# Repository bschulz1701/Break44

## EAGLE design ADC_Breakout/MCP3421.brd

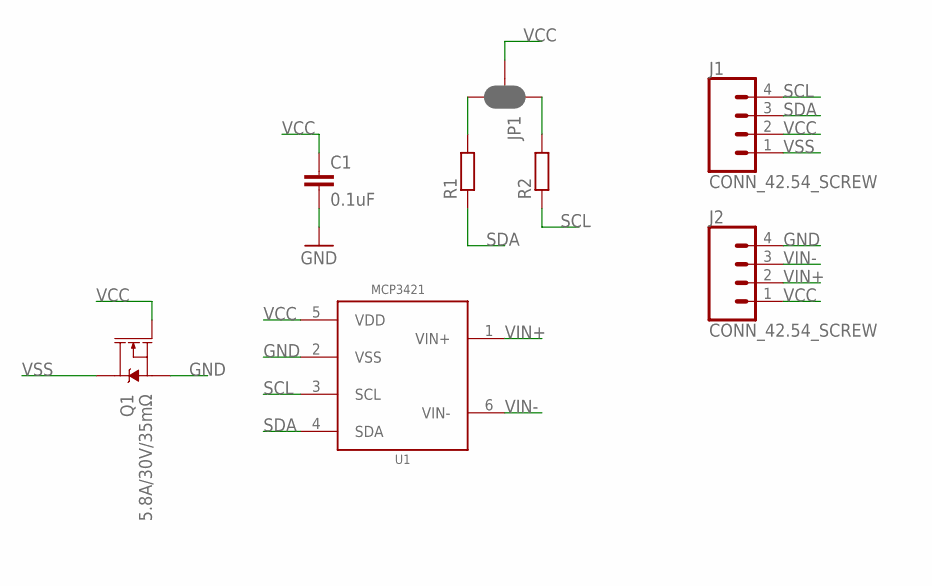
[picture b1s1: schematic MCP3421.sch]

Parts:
C1: 0.1uF; C0603
J1, J2: CONN_42.54_SCREW; 1X04_SCREW
JP1: JUMPER-SMT_3_2-NC_PASTE_SILK; SMT-JUMPER_3_2-NC_PASTE_SILK
Q1: 5.8A/30V/35mΩ; SOT23-3
R1, R2: R-EU_10KR0603; R0603
U1: MCP3421A3; SOT23-6L

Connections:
GND: C1.2, J2.4, Q1.2 (S), U1.2 (VSS)
unnamed: JP1.3, R1.2
unnamed: JP1.1, R2.2
SCL: J1.4, R2.1, U1.3 (SCL)
SDA: J1.3, R1.1, U1.4 (SDA)
VCC: C1.1, J1.2, J2.1, JP1.2, Q1.1 (G), U1.5 (VDD)
VIN+: J2.2, U1.1 (VIN+)
VIN-: J2.3, U1.6 (VIN-)
VSS: J1.1, Q1.3 (D)

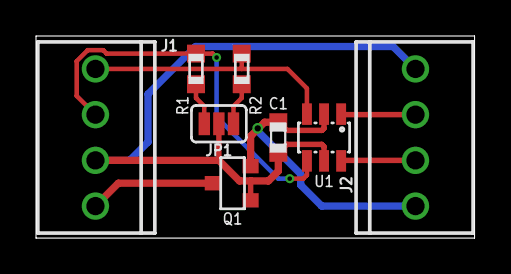
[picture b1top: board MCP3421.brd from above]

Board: 2 copper layers, 24.4 x 11.2 mm, 8 parts (0 on the bottom side), 9 nets.

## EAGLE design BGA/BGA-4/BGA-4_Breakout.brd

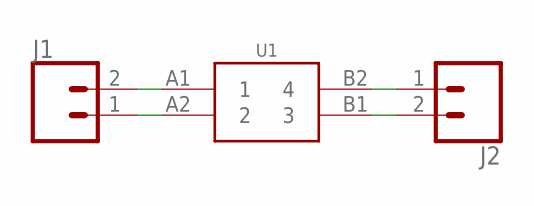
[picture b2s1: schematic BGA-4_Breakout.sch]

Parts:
J1, J2: CONN_02; 1X02
U1: GEN_4BGA; YFP0004

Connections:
unnamed: J2.1, U1.B2 (4)
unnamed: J2.2, U1.B1 (3)
unnamed: J1.1, U1.A2 (2)
unnamed: J1.2, U1.A1 (1)

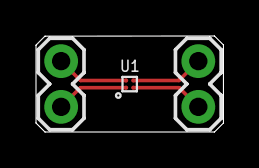
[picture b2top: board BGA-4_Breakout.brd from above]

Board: 2 copper layers, 10.4 x 5.3 mm, 3 parts (0 on the bottom side), 4 nets.

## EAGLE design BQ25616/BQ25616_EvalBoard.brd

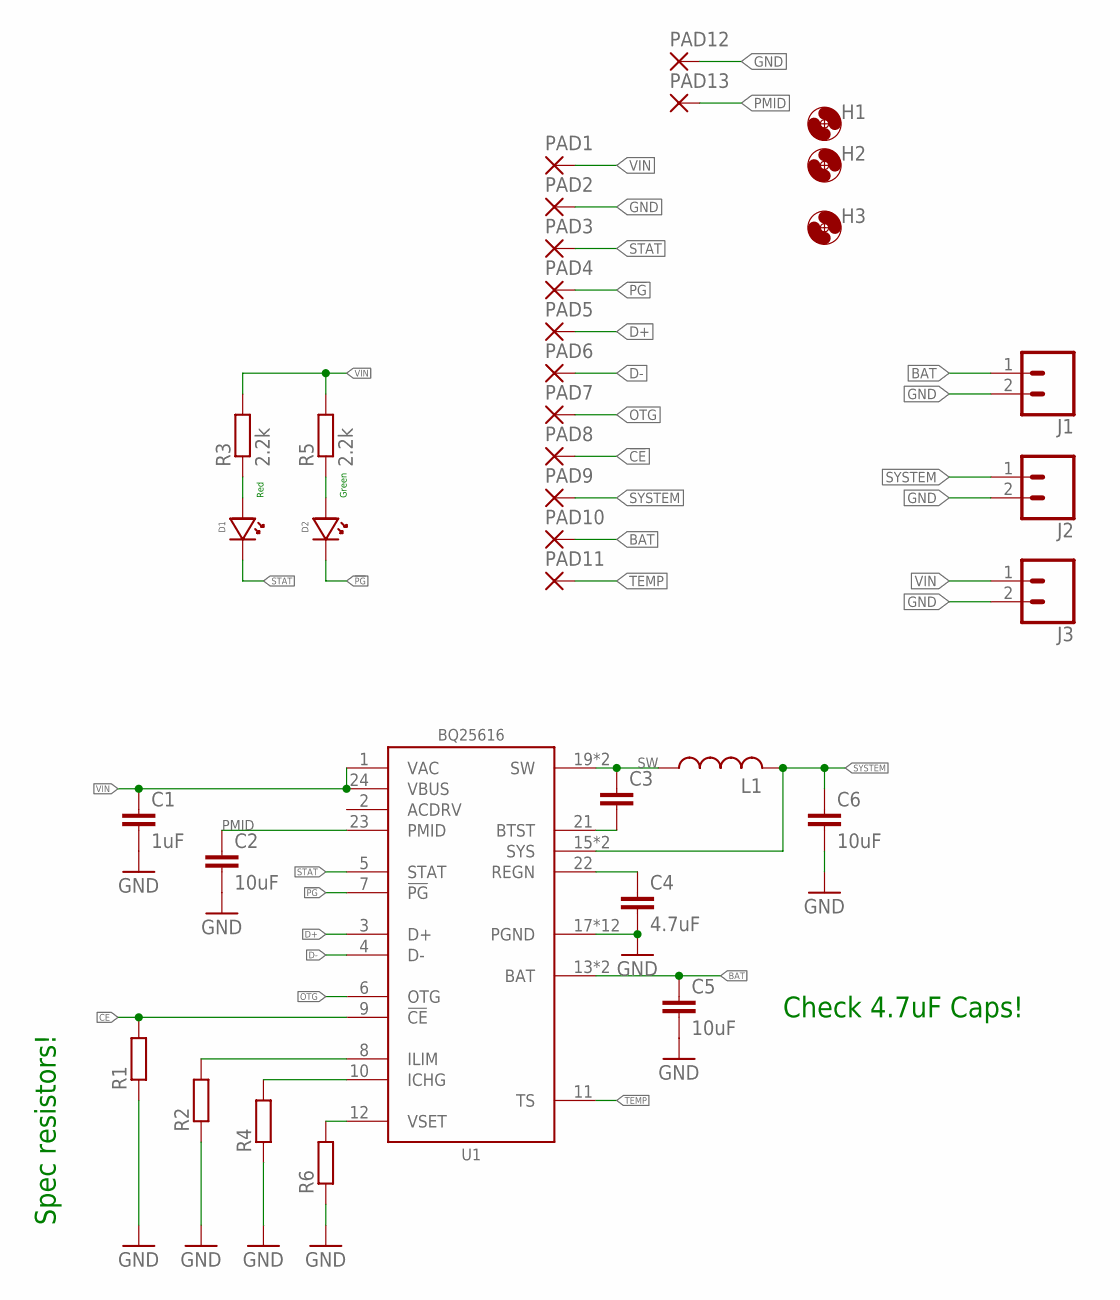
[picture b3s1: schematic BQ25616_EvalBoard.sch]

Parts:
C1: 1uF; C0603
C2, C5, C6: 10uF; C0805
C3: C-EUC0603; C0603
C4: 4.7uF; C0805
D1: LEDGREEN0603; LED_0603
D2: LEDRED0603; LED_0603
H1, H2, H3: MOUNTING_HOLE2_NP; 2_56
J1, J2, J3: CONN_023.5MM_ROUND_RESTRICT; SCREWTERMINAL-3.5MM-2_ROUND_RESTRICT
L1: INDUCTORMAIA_4.1X4.1; WE-MAIA(4.1X4.1)
PAD1, PAD2, PAD3, PAD4, PAD5, PAD6, PAD7, PAD8, PAD9, PAD10, PAD11, PAD12, PAD13: SMD1,27; SMD1,27-2,54
R1, R2, R4, R6: R-EU_R0603; R0603
R3, R5: 2.2k; R0603
U1: BQ25616; QFN24_POWER

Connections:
!CE: PAD8.1, R1.2, U1.9 (!CE)
!PG: D2.CATHODE, PAD4.1, U1.7 (!PG)
BAT: C5.1, J1.1, PAD10.1, U1.13 (BAT), U1.14 (BAT)
D+: PAD5.1, U1.3 (D+)
D-: PAD6.1, U1.4 (D-)
GND: C1.2, C2.2, C4.2, C5.2, C6.2, J1.2, J2.2, J3.2, PAD2.1, PAD12.1, R1.1, R2.1, R4.1, R6.1, U1.17 (PGND), U1.18 (PGND), U1.EP (PGND), U1.EP@1 (PGND), U1.EP@2 (PGND), U1.EP@3 (PGND), U1.EP@4 (PGND), U1.EP@5 (PGND), U1.EP@6 (PGND), U1.EP@7 (PGND), U1.EP@8 (PGND), U1.EP@9 (PGND)
unnamed: C4.1, U1.22 (REGN)
unnamed: C3.2, U1.21 (BTST)
unnamed: D2.ANODE, R5.1
unnamed: D1.ANODE, R3.1
unnamed: R6.2, U1.12 (VSET)
unnamed: R4.2, U1.10 (ICHG)
unnamed: R2.2, U1.8 (ILIM)
OTG: PAD7.1, U1.6 (OTG)
PMID: C2.1, PAD13.1, U1.23 (PMID)
STAT: D1.CATHODE, PAD3.1, U1.5 (STAT)
SW: C3.1, L1.P$1 (1), U1.19 (SW), U1.20 (SW)
SYSTEM: C6.1, J2.1, L1.P$2 (2), PAD9.1, U1.15 (SYS), U1.16 (SYS)
TEMP: PAD11.1, U1.11 (TS)
VIN: C1.1, J3.1, PAD1.1, R3.2, R5.2, U1.1 (VAC), U1.24 (VBUS)

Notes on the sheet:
Green
Red
Spec resistors!
Check 4.7uF Caps!

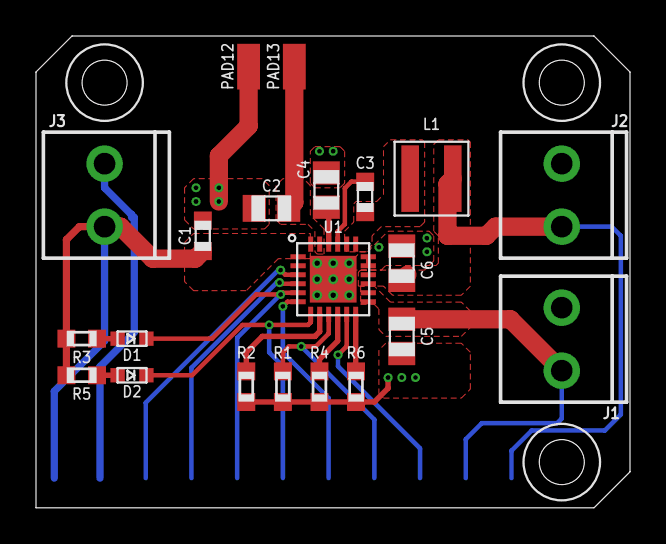
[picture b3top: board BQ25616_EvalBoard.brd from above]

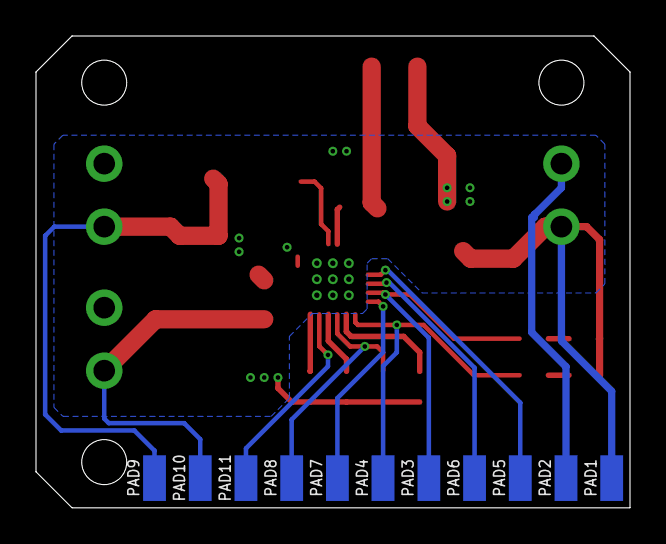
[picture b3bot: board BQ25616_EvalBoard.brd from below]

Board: 2 copper layers, 33.0 x 26.2 mm, 35 parts (11 on the bottom side), 20 nets.

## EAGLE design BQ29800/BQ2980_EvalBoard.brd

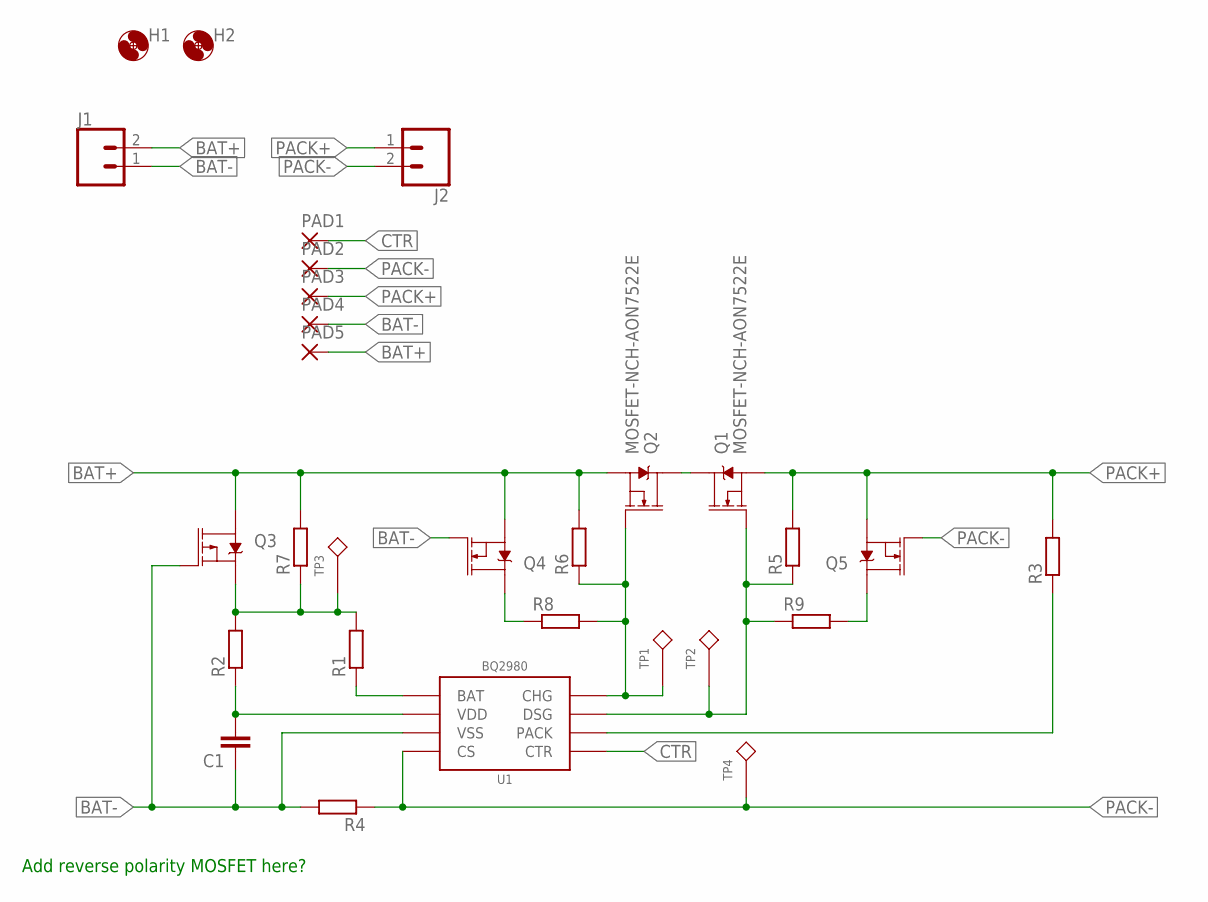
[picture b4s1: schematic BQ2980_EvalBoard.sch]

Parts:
C1: C-EUC0603; C0603
H1, H2: MOUNTING_HOLE2_NP; 2_56
J1, J2: CONN_023.5MM_ROUND_RESTRICT; SCREWTERMINAL-3.5MM-2_ROUND_RESTRICT
PAD1, PAD2, PAD3, PAD4, PAD5: SMD1,27; SMD1,27-2,54
Q1, Q2: MOSFET-NCH-AON7522E; DFN3X3A_8L_EP1_P
Q3: MOSFET_PCH-NX2301P; SOT23-3
Q4, Q5: 2N7002; SOT323
R1, R2, R3, R5, R6, R7, R8, R9: R-EU_R0603; R0603
R4: R-EU_R0805; R0805
TP1, TP2, TP3, TP4: TESTPOINTRCU; TESTPOINT_0603
U1: BQ2980RUG; RUG_S-PQFP-N8

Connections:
BAT+: J1.2, PAD5.1, Q2.S@1 (S), Q2.S@2 (S), Q2.S@3 (S), Q3.3 (D), Q4.2 (S), R6.2, R7.2
BAT-: C1.1, J1.1, PAD4.1, Q3.1 (G), Q4.1 (G), R4.2, U1.3 (VSS)
CHG: Q2.G, R6.1, R8.2, TP1.1, U1.8 (CHG)
CTR: PAD1.1, U1.5 (CTR)
DSG: Q1.G, R5.1, R9.1, TP2.1, U1.7 (DSG)
LOGIC_SUPPLY: Q3.2 (S), R1.2, R2.2, R7.1, TP3.1
unnamed: R3.1, U1.6 (PACK)
unnamed: C1.2, R2.1, U1.2 (VDD)
unnamed: R1.1, U1.1 (BAT)
unnamed: Q4.3 (D), R8.1
unnamed: Q5.3 (D), R9.2
unnamed: Q1.D, Q2.D
PACK+: J2.1, PAD3.1, Q1.S@1 (S), Q1.S@2 (S), Q1.S@3 (S), Q5.2 (S), R3.2, R5.2
PACK-: J2.2, PAD2.1, Q5.1 (G), R4.1, TP4.1, U1.4 (CS)

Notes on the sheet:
Add reverse polarity MOSFET here?

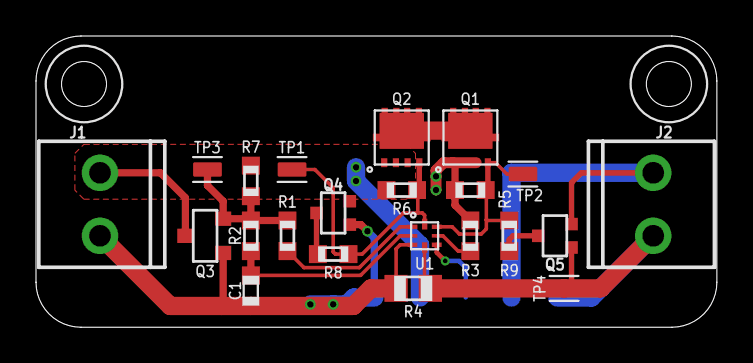
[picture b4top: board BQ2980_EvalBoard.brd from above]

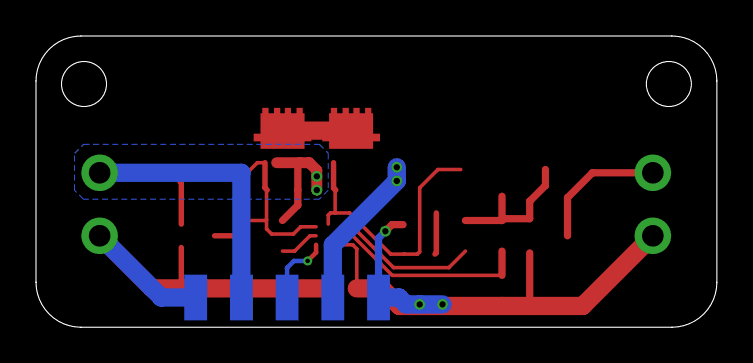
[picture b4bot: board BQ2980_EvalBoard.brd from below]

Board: 2 copper layers, 37.8 x 16.2 mm, 29 parts (5 on the bottom side), 14 nets.

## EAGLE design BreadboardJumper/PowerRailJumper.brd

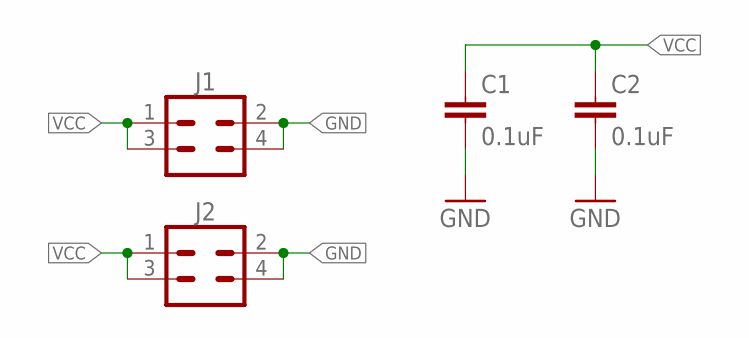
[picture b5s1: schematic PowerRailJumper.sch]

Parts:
C1, C2: 0.1uF; C0603
J1, J2: CONN_2X2; 2X02

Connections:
GND: C1.2, C2.2, J1.2, J1.4, J2.2, J2.4
VCC: C1.1, C2.1, J1.1, J1.3, J2.1, J2.3

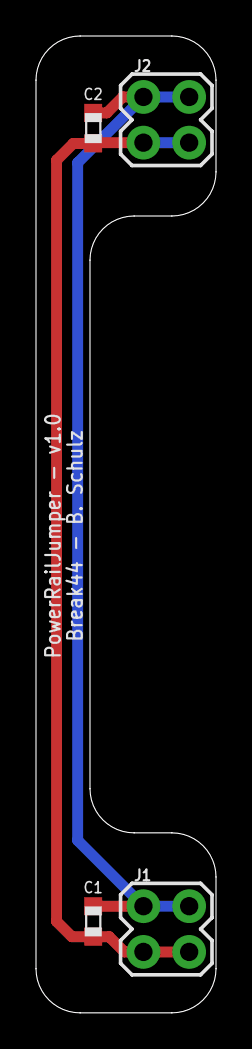
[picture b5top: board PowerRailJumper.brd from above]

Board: 2 copper layers, 10.0 x 54.3 mm, 4 parts (0 on the bottom side), 2 nets.

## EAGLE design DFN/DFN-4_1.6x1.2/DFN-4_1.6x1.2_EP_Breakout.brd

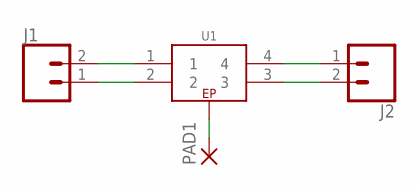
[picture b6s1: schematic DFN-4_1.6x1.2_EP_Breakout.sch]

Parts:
J1, J2: CONN_02; 1X02
PAD1: SMD2; SMD1,27-2,54
U1: GEN_4_EPTDFN_4; TDFN_4

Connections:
unnamed: PAD1.1, U1.EP
unnamed: J1.1, U1.2
unnamed: J1.2, U1.1
unnamed: J2.1, U1.4
unnamed: J2.2, U1.3

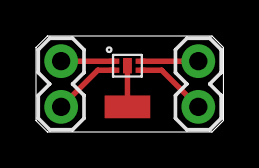
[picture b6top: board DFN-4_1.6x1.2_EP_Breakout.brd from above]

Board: 2 copper layers, 10.4 x 5.3 mm, 4 parts (0 on the bottom side), 5 nets.

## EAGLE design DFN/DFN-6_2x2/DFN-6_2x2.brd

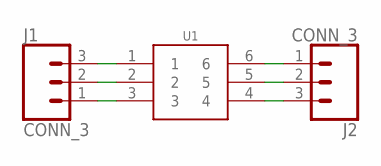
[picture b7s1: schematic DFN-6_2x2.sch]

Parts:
J1, J2: CONN_3; 1X03
U1: GEN_6DFN_2X2; DFN_6_2X2

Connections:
unnamed: J1.1, U1.3
unnamed: J1.2, U1.2
unnamed: J1.3, U1.1
unnamed: J2.3, U1.4
unnamed: J2.2, U1.5
unnamed: J2.1, U1.6

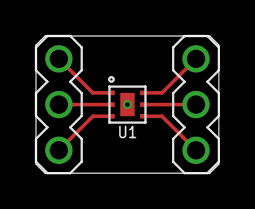
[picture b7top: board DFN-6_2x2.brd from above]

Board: 2 copper layers, 10.2 x 7.6 mm, 3 parts (0 on the bottom side), 6 nets.

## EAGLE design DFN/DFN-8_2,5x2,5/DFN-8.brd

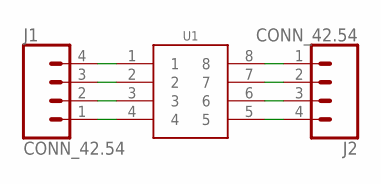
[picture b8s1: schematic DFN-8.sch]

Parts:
J1, J2: CONN_42.54; 1X04
U1: GEN_8DFN; DFN_8_2.5X2.5

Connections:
unnamed: J1.1, U1.4
unnamed: J1.2, U1.3
unnamed: J1.3, U1.2
unnamed: J1.4, U1.1
unnamed: J2.4, U1.5
unnamed: J2.3, U1.6
unnamed: J2.2, U1.7
unnamed: J2.1, U1.8

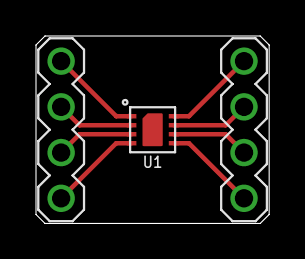
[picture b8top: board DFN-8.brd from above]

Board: 2 copper layers, 13.0 x 10.4 mm, 3 parts (0 on the bottom side), 8 nets.

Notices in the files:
parts and their libraries:
SparkFun-Jumpers: Licensing: Creative Commons ShareAlike 4.0 International - https://creativecommons.org/licenses/by-sa/4.0
